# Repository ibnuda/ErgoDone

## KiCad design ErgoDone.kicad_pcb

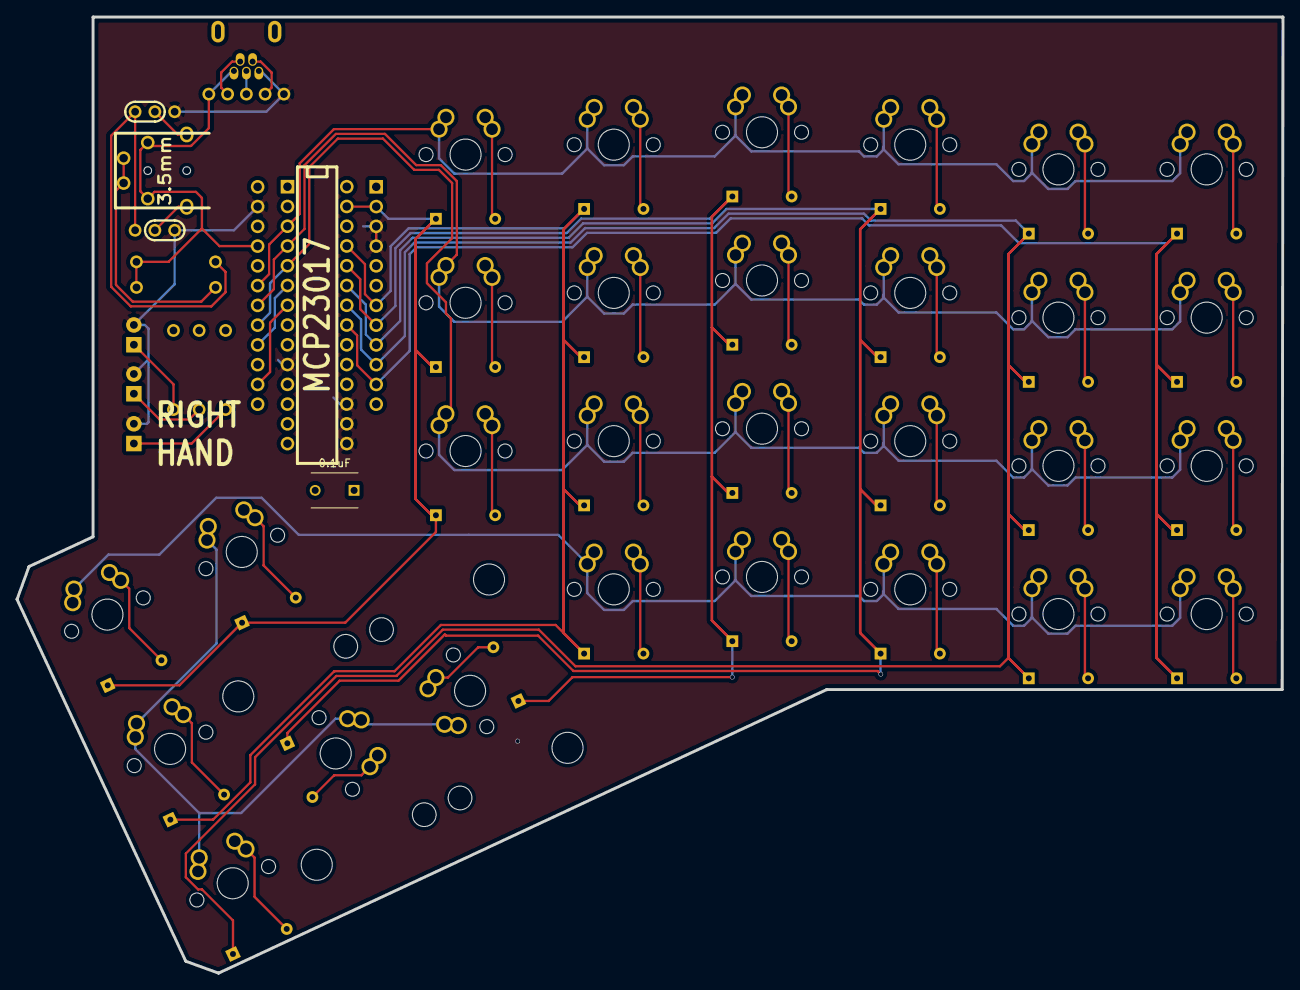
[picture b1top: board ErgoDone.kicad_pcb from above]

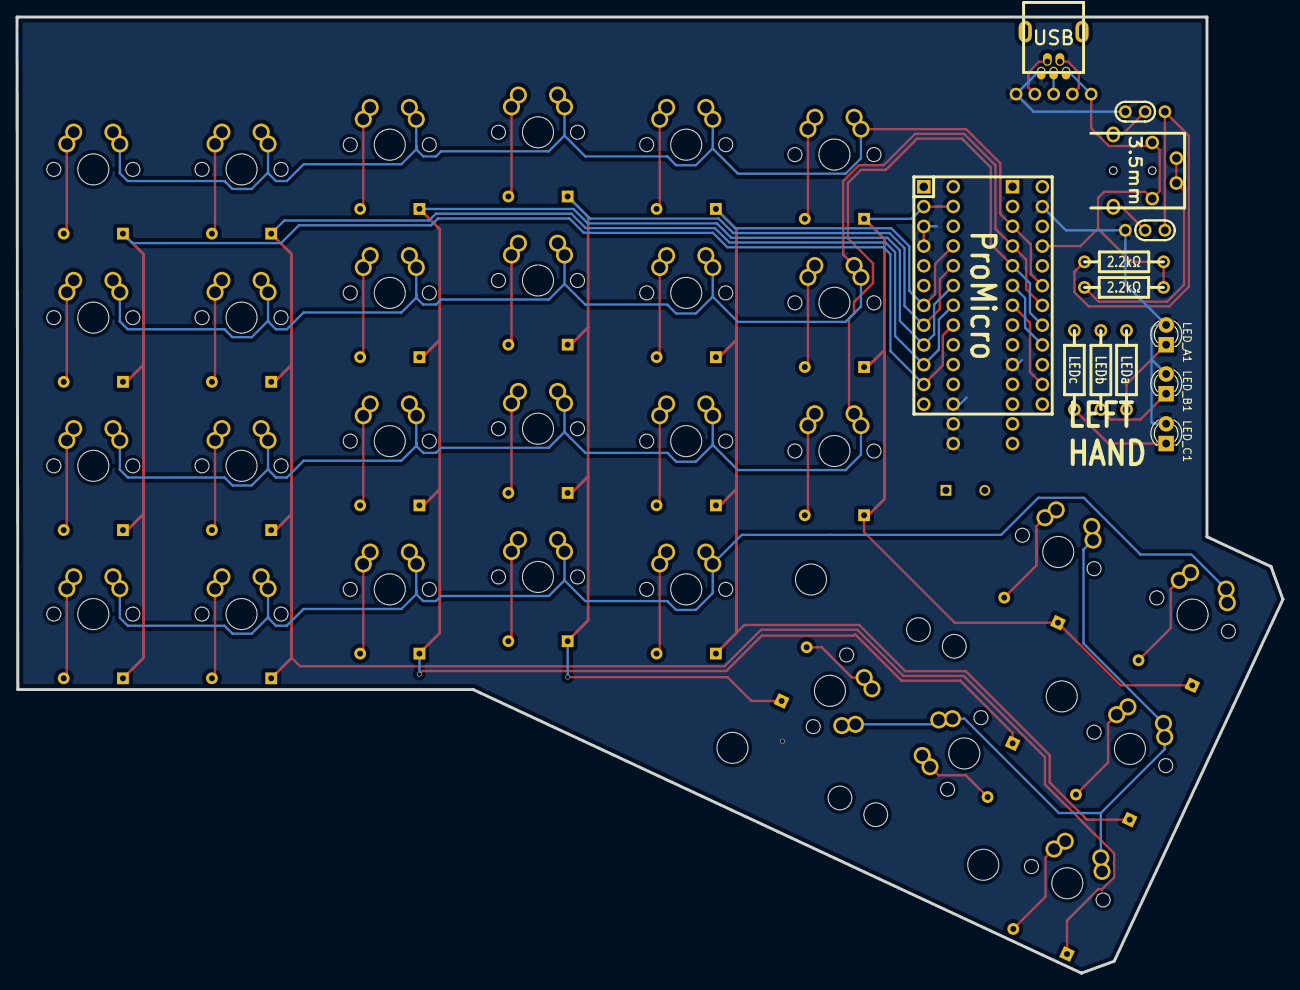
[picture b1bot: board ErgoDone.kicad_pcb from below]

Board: 2 copper layers, 162.7 x 122.9 mm, 44 parts (11 on the bottom side), 52 nets.

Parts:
C1: 0.1uF; C_Disc_D6_P5
J1: USB; USBMINImod
J2: 3.5mm; 4pin35mmAudio
J3, J4: JMP; 100PITCH1X3
LED_A1: LEDa; ERGO_LED-3MM
LED_B1: LEDb; ERGO_LED-3MM
LED_C1: LEDc; ERGO_LED-3MM
R1, R2: 2.2kΩ; ERGO_RESISTOR
RA1: LEDa; ERGO_RESISTOR
RB1: LEDb; ERGO_RESISTOR
RC1: LEDc; ERGO_RESISTOR
SW0:8: SW0:5; 100-dual
SW0:9: SW0:4; 100-dual
SW0:10: SW0:3; 200-dual
SW0:11: SW0:2; 200-dual
SW0:12: SW0:1; 100-dual
SW1:9: SW1:4; 100-dual
SW1:10: SW1:3; 100-dual
SW1:11: SW1:2; 100-dual
SW1:12: SW1:1; 100-dual
SW1:13: SW1:0; 100-dual
SW2:8: SW2:5; 100-dual
SW2:9: SW2:4; 100-dual
SW2:10: SW2:3; 100-dual
SW2:11: SW2:2; 100-dual
SW2:12: SW2:1; 100-dual
SW2:13: SW2:0; 100-dual
SW3:8: SW3:5; 100-dual
SW3:9: SW3:4; 100-dual
SW3:10: SW3:3; 100-dual
SW3:11: SW3:2; 100-dual
SW3:12: SW3:1; 100-dual
SW3:13: SW3:0; 100-dual
SW4:8: SW4:5; 100-dual
SW4:9: SW4:4; 100-dual
SW4:10: SW4:3; 100-dual
SW4:11: SW4:2; 100-dual
SW4:12: SW4:1; 100-dual
SW4:13: SW4:0; 100-dual
SX1:8: SX1:5; 100-dual
U1: ProMicro
U2: MCP23017

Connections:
/COL0: SW1:13.4, SW2:13.4, SW3:13.4, SW4:13.4, U1.11, U2.21
/COL1: SW0:12.4, SW1:12.4, SW2:12.4, SW3:12.4, SW4:12.4, U1.10, U2.22
/COL4: SW0:9.4, SW1:9.4, SW2:9.4, SW3:9.4, SW4:9.4, U1.7, U2.25
/COL5: SW0:8.4, SW2:8.4, SW3:8.4, SW4:8.4, SX1:8.4, U1.2, U2.27
/COL10: SW0:10.4, SW1:10.4, SW2:10.4, SW3:10.4, SW4:10.4, U1.8, U2.24
/COL11: SW0:11.4, SW1:11.4, SW2:11.4, SW3:11.4, SW4:11.4, U1.9, U2.23
/LED_A: RA1.1, U1.12
/LED_B: RB1.1, U1.18
/LED_C: RC1.1, U1.20
/ROW0: SW0:8.1, SW0:9.1, SW0:10.1, SW0:11.1, SW0:12.1, U1.19, U2.7
/ROW1: SW1:9.1, SW1:10.1, SW1:11.1, SW1:12.1, SW1:13.1, SX1:8.1, U1.21, U2.6
/ROW2: SW2:8.1, SW2:9.1, SW2:10.1, SW2:11.1, SW2:12.1, SW2:13.1, U1.22, U2.5
/ROW3: SW3:8.1, SW3:9.1, SW3:10.1, SW3:11.1, SW3:12.1, SW3:13.1, U1.23, U2.4
/ROW4: SW4:8.1, SW4:9.1, SW4:10.1, SW4:11.1, SW4:12.1, SW4:13.1, U1.24, U2.3
/SCLM: J2.3, J2.5, R2.2, U1.6, U2.12
/SDAM: J3.1, J4.1, R1.2, U1.5, U2.13
GND: J1.5, J3.3, J4.3, LED_A1.2, LED_B1.2, LED_C1.2, U1.3, U1.4, U1.28, U2.10, U2.15, U2.16, U2.17
unnamed: J2.1, J3.2
unnamed: J2.4, J4.2
unnamed: LED_A1.1, RA1.2
unnamed: LED_B1.1, RB1.2
unnamed: LED_C1.1, RC1.2
unnamed: SW0:8.2, SW0:8.3
unnamed: SW0:9.2, SW0:9.3
unnamed: SW0:10.2, SW0:10.3
unnamed: SW0:11.2, SW0:11.3
unnamed: SW0:12.2, SW0:12.3
unnamed: SW1:9.2, SW1:9.3
unnamed: SW1:10.2, SW1:10.3
unnamed: SW1:11.2, SW1:11.3
unnamed: SW1:12.2, SW1:12.3
unnamed: SW1:13.2, SW1:13.3
unnamed: SW2:8.2, SW2:8.3
unnamed: SW2:9.2, SW2:9.3
unnamed: SW2:10.2, SW2:10.3
unnamed: SW2:11.2, SW2:11.3
unnamed: SW2:12.2, SW2:12.3
unnamed: SW2:13.2, SW2:13.3
unnamed: SW3:8.2, SW3:8.3
unnamed: SW3:9.2, SW3:9.3
unnamed: SW3:10.2, SW3:10.3
unnamed: SW3:11.2, SW3:11.3
unnamed: SW3:12.2, SW3:12.3
unnamed: SW3:13.2, SW3:13.3
unnamed: SW4:8.2, SW4:8.3
unnamed: SW4:9.2, SW4:9.3
unnamed: SW4:10.2, SW4:10.3
unnamed: SW4:11.2, SW4:11.3
unnamed: SW4:12.2, SW4:12.3
unnamed: SW4:13.2, SW4:13.3
unnamed: SX1:8.2, SX1:8.3
VCC: J1.1, J2.2, J2.6, R1.1, R2.1, U1.26, U2.9, U2.18

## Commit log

2021-07-04 what
2021-07-05 whatever
